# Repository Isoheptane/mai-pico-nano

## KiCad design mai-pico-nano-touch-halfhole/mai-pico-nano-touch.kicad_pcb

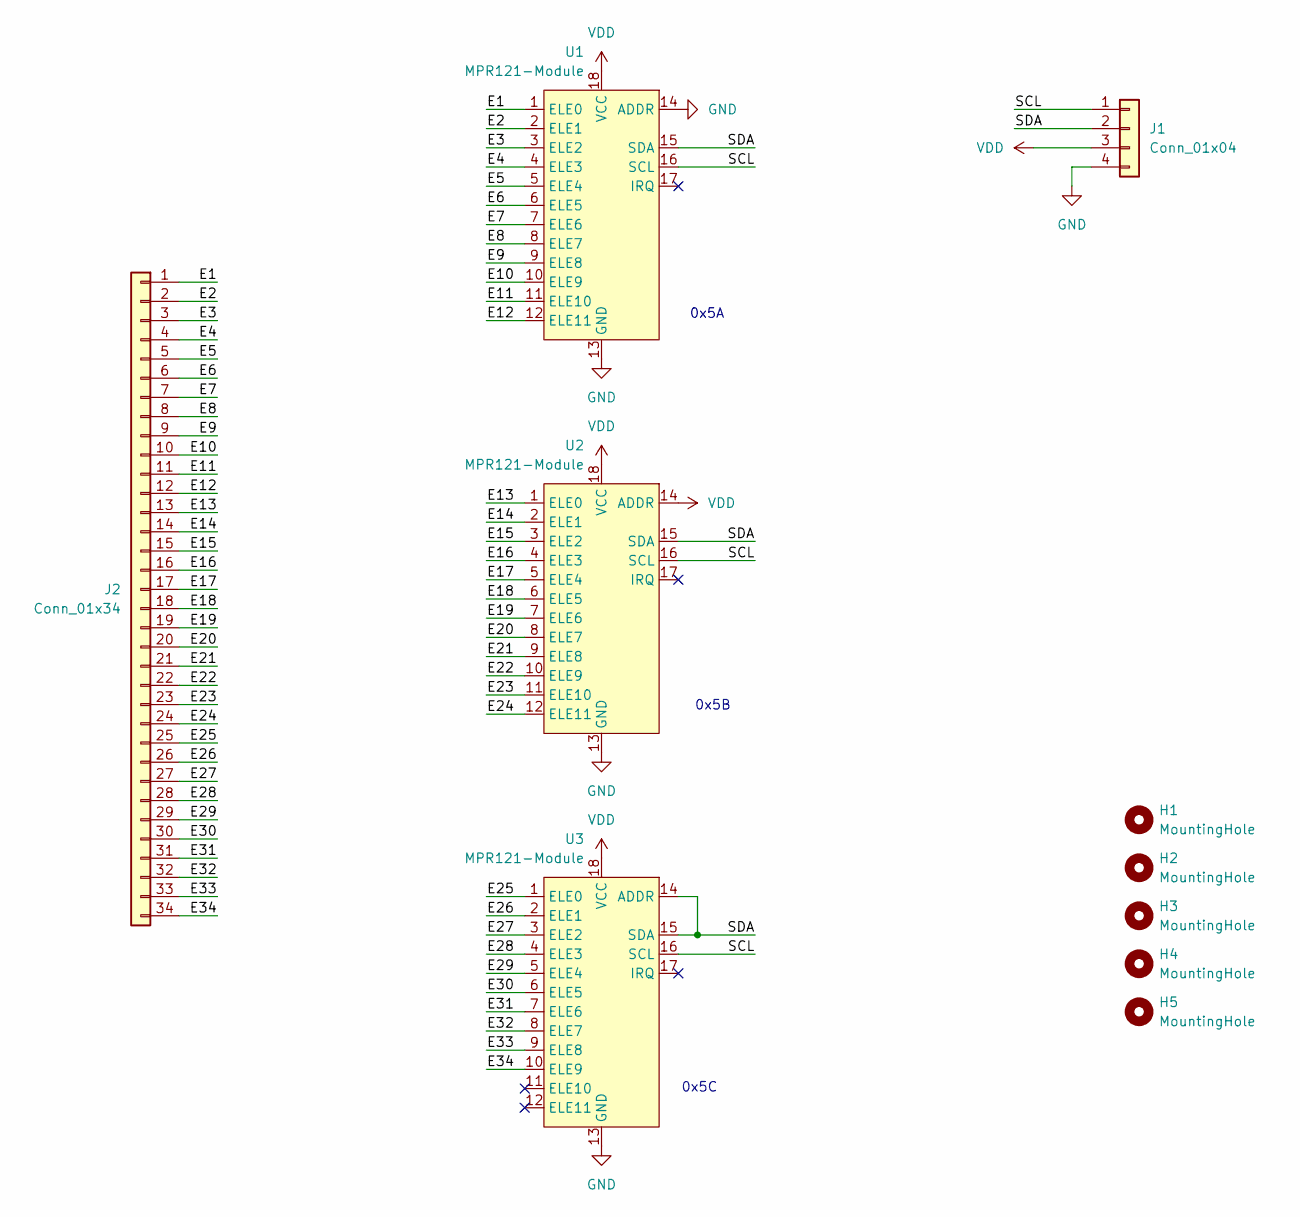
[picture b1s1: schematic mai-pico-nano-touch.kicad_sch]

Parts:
H1, H2, H3, H4, H5: MountingHole; MountingHole_2.2mm_M2
J1: Conn_01x04; Molex_PicoBlade_53048-0410_1x04_P1.25mm_Horizontal
J2: Conn_01x34; TouchSensors
U1, U2, U3: MPR121-Module

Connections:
/E1: J2.1, U1.1 (ELE0)
/E2: J2.2, U1.2 (ELE1)
/E3: J2.3, U1.3 (ELE2)
/E4: J2.4, U1.4 (ELE3)
/E5: J2.5, U1.5 (ELE4)
/E6: J2.6, U1.6 (ELE5)
/E7: J2.7, U1.7 (ELE6)
/E8: J2.8, U1.8 (ELE7)
/E9: J2.9, U1.9 (ELE8)
/E10: J2.10, U1.10 (ELE9)
/E11: J2.11, U1.11 (ELE10)
/E12: J2.12, U1.12 (ELE11)
/E13: J2.13, U2.1 (ELE0)
/E14: J2.14, U2.2 (ELE1)
/E15: J2.15, U2.3 (ELE2)
/E16: J2.16, U2.4 (ELE3)
/E17: J2.17, U2.5 (ELE4)
/E18: J2.18, U2.6 (ELE5)
/E19: J2.19, U2.7 (ELE6)
/E20: J2.20, U2.8 (ELE7)
/E21: J2.21, U2.9 (ELE8)
/E22: J2.22, U2.10 (ELE9)
/E23: J2.23, U2.11 (ELE10)
/E24: J2.24, U2.12 (ELE11)
/E25: J2.25, U3.1 (ELE0)
/E26: J2.26, U3.2 (ELE1)
/E27: J2.27, U3.3 (ELE2)
/E28: J2.28, U3.4 (ELE3)
/E29: J2.29, U3.5 (ELE4)
/E30: J2.30, U3.6 (ELE5)
/E31: J2.31, U3.7 (ELE6)
/E32: J2.32, U3.8 (ELE7)
/E33: J2.33, U3.9 (ELE8)
/E34: J2.34, U3.10 (ELE9)
/SCL: J1.1, U1.16 (SCL), U2.16 (SCL), U3.16 (SCL)
/SDA: J1.2, U1.15 (SDA), U2.15 (SDA), U3.14 (ADDR), U3.15 (SDA)
GND: J1.4, U1.13 (GND), U1.14 (ADDR), U2.13 (GND), U3.13 (GND)
VDD: J1.3, U1.18 (VCC), U2.14 (ADDR), U2.18 (VCC), U3.18 (VCC)

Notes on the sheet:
0x5B
0x5A
0x5C

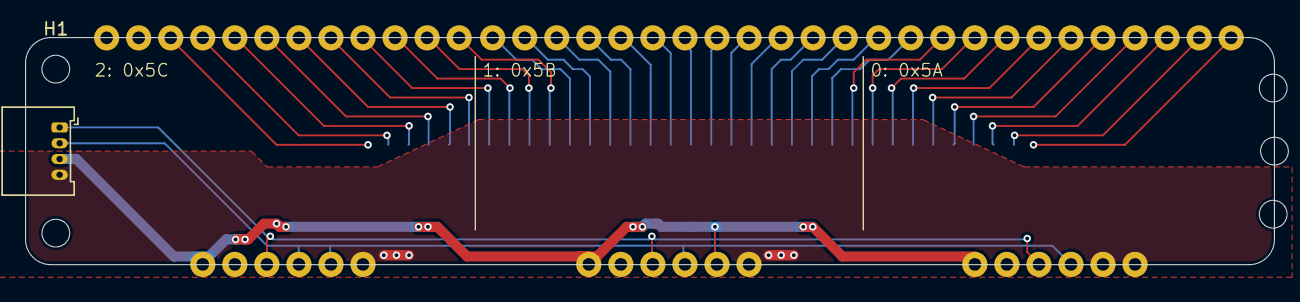
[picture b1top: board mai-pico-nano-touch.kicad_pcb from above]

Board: 2 copper layers, 99.0 x 18.0 mm, 10 parts (1 on the bottom side), 38 nets.

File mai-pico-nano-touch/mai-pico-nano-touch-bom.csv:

"Id";"Designator";"Footprint";"Quantity";"Designation";"Supplier and ref";
1;"U1,U2,U3";"MPR121-Module-SMD";3;"MPR121-Module";;;
2;"J1";"Molex_PicoBlade_53048-0410_1x04_P1.25mm_Horizontal";1;"Conn_01x04";;;
3;"J2";"TouchSensors";1;"Conn_01x34";;;

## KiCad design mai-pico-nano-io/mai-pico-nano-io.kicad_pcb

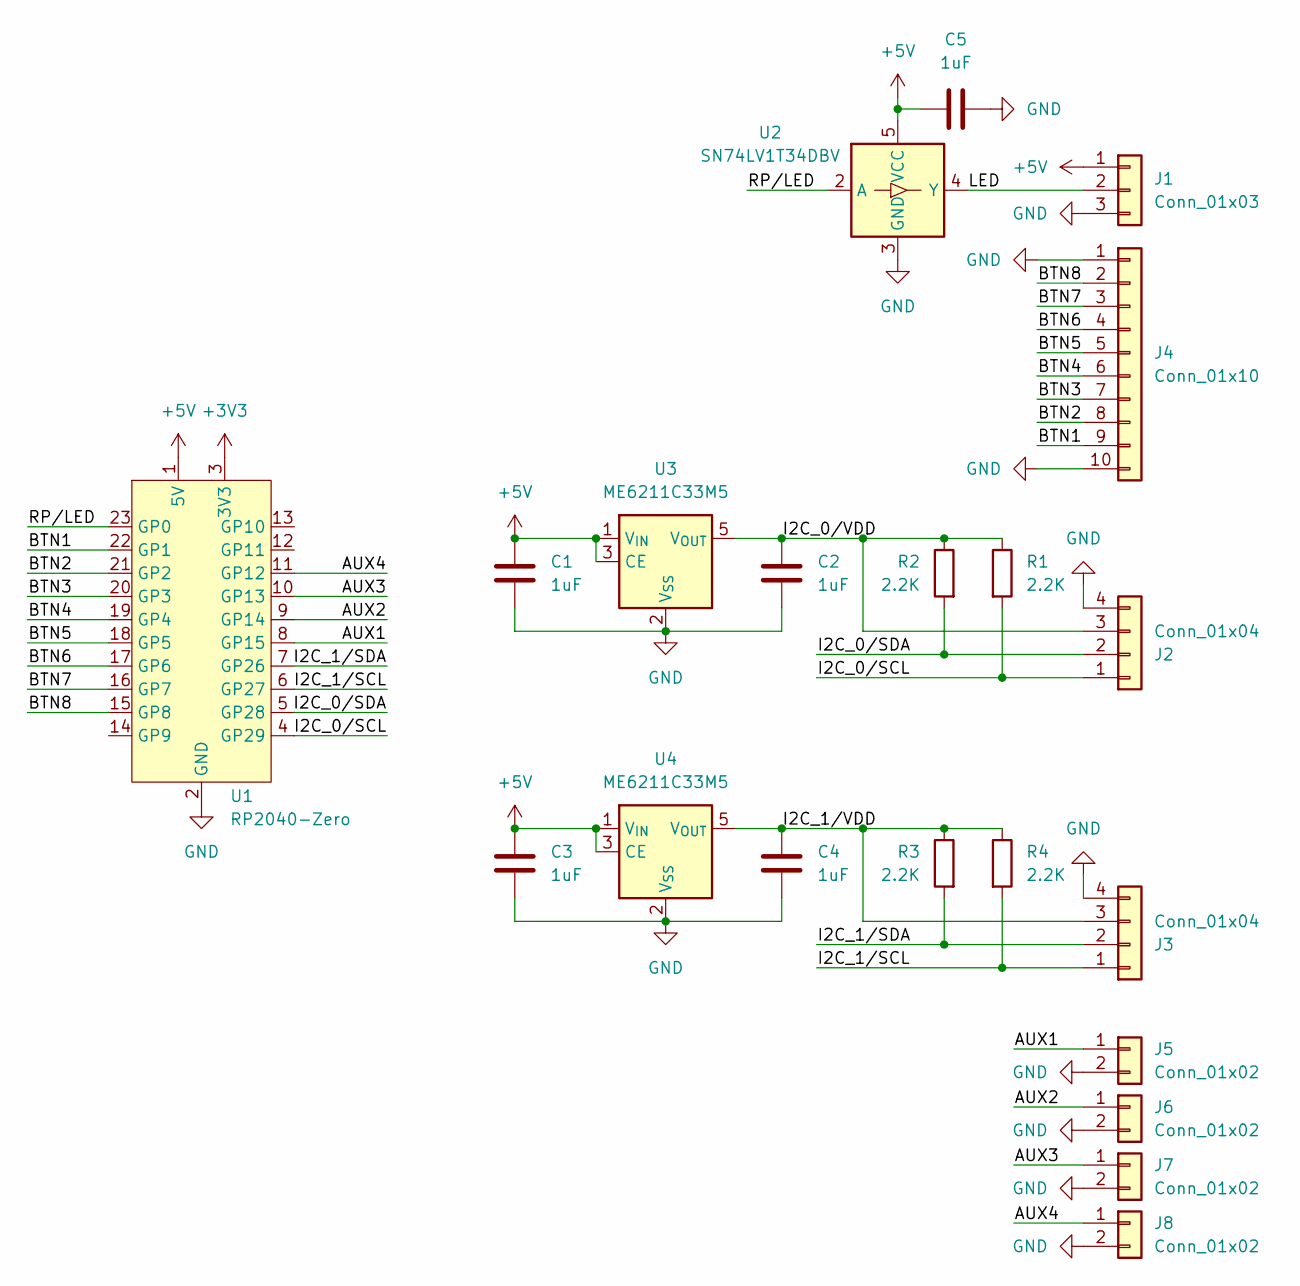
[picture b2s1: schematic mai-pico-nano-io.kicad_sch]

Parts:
C1, C2, C3, C4, C5: 1uF; C_0603_1608Metric
J1: Conn_01x03; Molex_PicoBlade_53048-0310_1x03_P1.25mm_Horizontal
J2, J3: Conn_01x04; Molex_PicoBlade_53048-0410_1x04_P1.25mm_Horizontal
J4: Conn_01x10; Molex_PicoBlade_53048-1010_1x10_P1.25mm_Horizontal
J5, J6, J7, J8: Conn_01x02; Molex_PicoBlade_53048-0210_1x02_P1.25mm_Horizontal
R1, R2, R3, R4: 2.2K; R_0603_1608Metric
U1: RP2040-Zero
U2: SN74LV1T34DBV; SOT-23-5
U3, U4: ME6211C33M5; SOT-23-5

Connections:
+3V3: U1.3 (3V3)
+5V: C1.1, C3.1, C5.1, J1.1, U1.1 (5V), U2.5 (VCC), U3.1 (V_{IN}), U3.3 (CE), U4.1 (V_{IN}), U4.3 (CE)
/AUX1: J5.1, U1.8 (GP15)
/AUX2: J6.1, U1.9 (GP14)
/AUX3: J7.1, U1.10 (GP13)
/AUX4: J8.1, U1.11 (GP12)
/BTN1: J4.9, U1.22 (GP1)
/BTN2: J4.8, U1.21 (GP2)
/BTN3: J4.7, U1.20 (GP3)
/BTN4: J4.6, U1.19 (GP4)
/BTN5: J4.5, U1.18 (GP5)
/BTN6: J4.4, U1.17 (GP6)
/BTN7: J4.3, U1.16 (GP7)
/BTN8: J4.2, U1.15 (GP8)
/I2C_0/SCL: J2.1, R1.2, U1.4 (GP29)
/I2C_0/SDA: J2.2, R2.2, U1.5 (GP28)
/I2C_0/VDD: C2.1, J2.3, R1.1, R2.1, U3.5 (V_{OUT})
/I2C_1/SCL: J3.1, R4.2, U1.6 (GP27)
/I2C_1/SDA: J3.2, R3.2, U1.7 (GP26)
/I2C_1/VDD: C4.1, J3.3, R3.1, R4.1, U4.5 (V_{OUT})
/LED: J1.2, U2.4 (Y)
/RP/LED: U1.23 (GP0), U2.2 (A)
GND: C1.2, C2.2, C3.2, C4.2, C5.2, J1.3, J2.4, J3.4, J4.1, J4.10, J5.2, J6.2, J7.2, J8.2, U1.2 (GND), U2.3 (GND), U3.2 (V_{SS}), U4.2 (V_{SS})

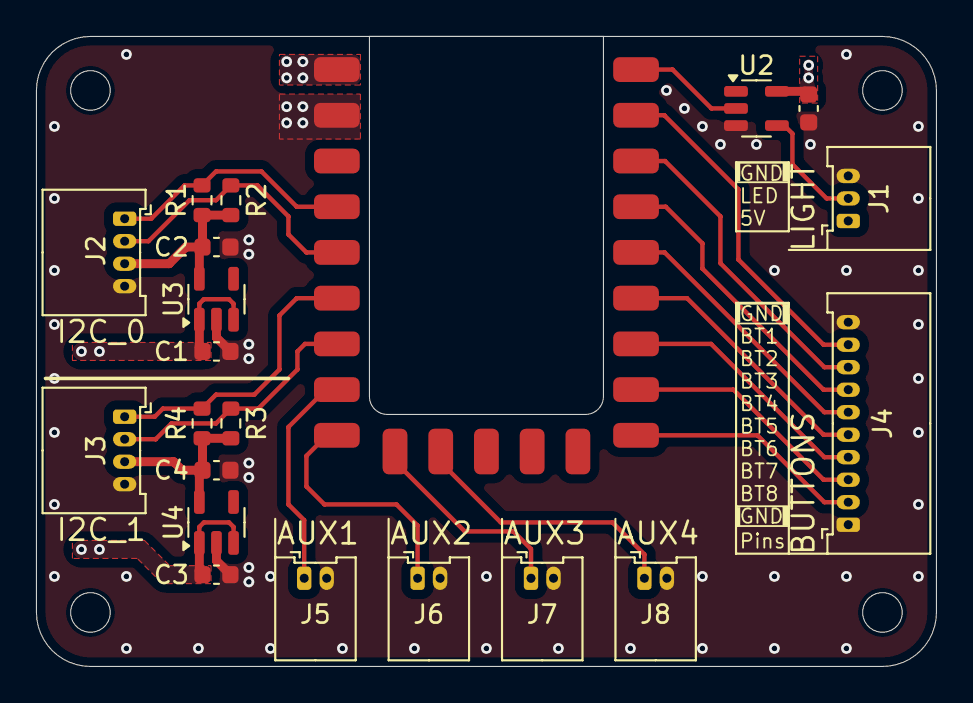
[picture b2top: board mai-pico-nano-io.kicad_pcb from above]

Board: 2 copper layers, 50.0 x 35.0 mm, 21 parts (0 on the bottom side), 22 nets.

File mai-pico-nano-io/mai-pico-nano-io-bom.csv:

"Id";"Designator";"Footprint";"Quantity";"Designation";"Supplier and ref";
1;"J3,J2";"Molex_PicoBlade_53048-0410_1x04_P1.25mm_Horizontal";2;"Conn_01x04";;;
2;"J4";"Molex_PicoBlade_53048-1010_1x10_P1.25mm_Horizontal";1;"Conn_01x10";;;
3;"U3,U4";"SOT-23-5";2;"ME6211C33M5";;;
4;"R4,R3,R1,R2";"R_0603_1608Metric";4;"2.2K";;;
5;"C3,C4,C5,C2,C1";"C_0603_1608Metric";5;"1uF";;;
6;"U1";"RP2040-Zero";1;"RP2040-Zero";;;
7;"U2";"SOT-23-5";1;"SN74LV1T34DBV";;;
8;"J7,J8,J6,J5";"Molex_PicoBlade_53048-0210_1x02_P1.25mm_Horizontal";4;"Conn_01x02";;;
9;"J1";"Molex_PicoBlade_53048-0310_1x03_P1.25mm_Horizontal";1;"Conn_01x03";;;

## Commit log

2024-08-03 Upload mai-pico-nano
2024-08-03 Add screwholes to touch board
2024-08-04 Add gerber files
2024-08-04 Add bom files
2024-08-10 Update touch board silkscreen
2025-02-28 Fix PCB not connected
2025-03-12 Update Half Hole version
2025-03-12 Half Hole version mounting holes
